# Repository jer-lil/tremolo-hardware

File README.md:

This is the hardware (PCB, MCAD) design for a tremolo pedal for guitar (or bass, synth, tonewheel organ, whatever you like). 
The firmware is here: https://github.com/jer-lil/tremolo-firmware/tree/main

This tremolo packs a lot of features into a very small (Hammond 125B, 65x120mm) enclosure.
Features include:

- All analog signal path
- Full stereo, with dedicated 1/4" jacks
- Harmonic tremolo
  - Continually adjustable LFO phase, allowing for sounds between mono/stereo/harmonic not found in other tremolo pedals (that I've discovered, please let me know if you know of any)
- Envelope control
  - The louder you play, the faster the tremolo goes. Or slower. Or stronger. Or the triangle wave warps towards a sawtooth. You decide.
- Expression pedal control
- Tap Tempo
  - Optional external tap signal
- "Ramp" mode, allowing user to ramp the rate up or down using a footswitch
- MIDI control

Note that at the time of writing, this project is still in progress.
As such, I have not been focusing on public documentation. If you have questions, please reach out.

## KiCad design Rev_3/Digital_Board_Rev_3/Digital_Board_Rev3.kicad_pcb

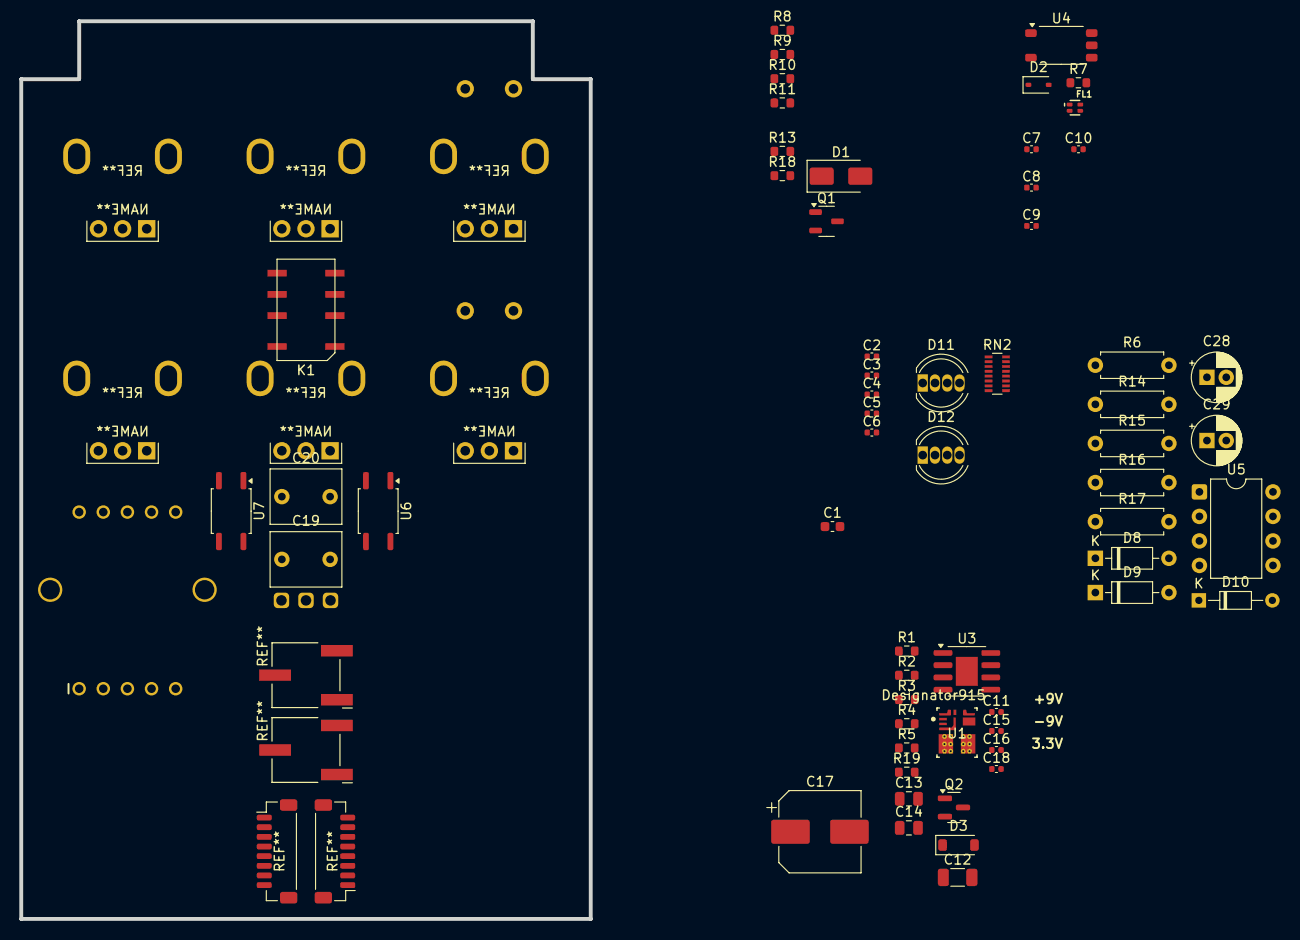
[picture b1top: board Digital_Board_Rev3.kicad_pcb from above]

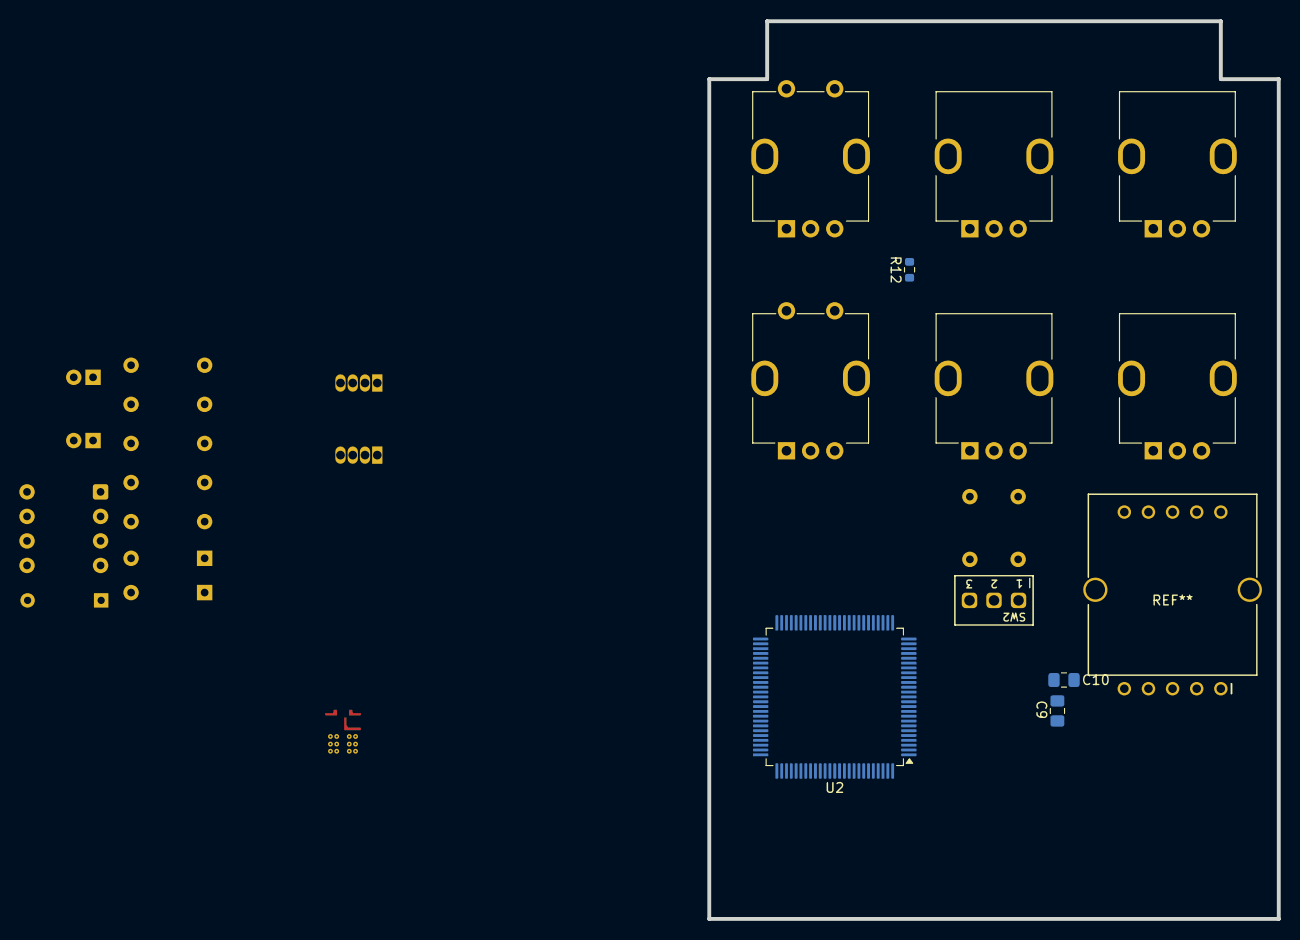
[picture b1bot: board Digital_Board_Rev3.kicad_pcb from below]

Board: 4 copper layers, 59.0 x 93.0 mm, 64 parts (5 on the bottom side), 41 nets, no tracks yet.

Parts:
C1: 2.2u; C_0603_1608Metric
C2, C3, C4, C5, C6, C7, C8, C9, C10, C16: 100n; C_0402_1005Metric
C9#2: 10n; C_0805_2012Metric_Pad1.18x1.45mm_HandSolder
C10#2: 1u; C_0805_2012Metric_Pad1.18x1.45mm_HandSolder
C11: 33n; C_0402_1005Metric
C12: 22u; C_1206_3216Metric
C13, C14: 10u; C_0805_2012Metric
C15: 1n; C_0402_1005Metric
C17: 100u; CP_Elec_8x6.2
C18: 22p; C_0402_1005Metric
C19, C20: 1u; C_Rect_L7.2mm_W5.5mm_P5.00mm_FKS2_FKP2_MKS2_MKP2
C28: 4.7u; CP_Radial_D5.0mm_P2.00mm
C29: 47u; CP_Radial_D5.0mm_P2.00mm
D1: B120-E3; D_SMA
D2: BAT54WS; D_SOD-323
D3: MMSZ5236B-7-F; D_SOD-123
D8, D9: 1N914; D_DO-35_SOD27_P7.62mm_Horizontal
D10: D_Zener; D_DO-34_SOD68_P7.62mm_Horizontal
D11, D12: LED_RGBA; LED_D5.0mm-4_RGB
FL1: FIL_EXC-24CB102U
K1: IM05GR; Relay_DPDT_TE_IM05GR
Q1: MMBT3904; SOT-23-3
Q2: DMP3099L; SOT-23
R1: 1; R_0603_1608Metric
R2: 180k; R_0603_1608Metric
R3: 43k; R_0603_1608Metric
R4: 68k; R_0603_1608Metric
R5: 15k; R_0603_1608Metric
R6: 3.3k; R_Axial_DIN0207_L6.3mm_D2.5mm_P7.62mm_Horizontal
R7, R9, R10: 330; R_0603_1608Metric
R8: 4.7k; R_0603_1608Metric
R11, R12: 1k; R_0603_1608Metric
R13, R18: 1M; R_0603_1608Metric
R14: 100k; R_Axial_DIN0207_L6.3mm_D2.5mm_P7.62mm_Horizontal
R15: 10k; R_Axial_DIN0207_L6.3mm_D2.5mm_P7.62mm_Horizontal
R16: 47k; R_Axial_DIN0207_L6.3mm_D2.5mm_P7.62mm_Horizontal
R17: 1k; R_Axial_DIN0207_L6.3mm_D2.5mm_P7.62mm_Horizontal
R19: 10k; R_0603_1608Metric
RN2: R_Pack08; R_Array_Convex_8x0602
SW2: SW_SPDT_MSM; SW_TOGGLE_ALPHA-200_SUBMINI_SPDT_PC-PINS
U1: TPSM84338RCJR; TI-RCJ0009A-MFG
U2: STM32G474VBTx; LQFP-100_14x14mm_P0.5mm
U3: ADP7142ARDZ; SOIC-8-1EP_3.9x4.9mm_P1.27mm_EP2.29x3mm
U4: TLP2361; SO-5-6_4.55x3.7mm_P1.27mm
U5: OPA2134; DIP-8_W7.62mm
U6, U7: TLP170AM; SO-4_4.4x3.9mm_P2.54mm

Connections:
+3.3V: R1.2, U4.6 (VDD)
+3V3: C1.1, C2.1, C3.1, C4.1, C5.1, C6.1, C9#2.1, C10#2.1, D11.4 (A), D12.4 (A), U2.24 (VDD), U2.37 (VDDA), U2.49 (VDD), U2.64 (VDD), U2.75 (VDD), U2.100 (VDD)
+9V: D1.1 (K), K1.1
/ENVELOPE/ENV_OUT: C29.2, D10.1 (K), R17.2
/Optos and LEDs/B1_R: D12.3 (BK), RN2.11 (R6.2)
/Optos and LEDs/B2_R: D11.3 (BK), RN2.14 (R3.2)
/Optos and LEDs/G1_R: D12.2 (GK), RN2.12 (R5.2)
/Optos and LEDs/G2_R: D11.2 (GK), RN2.15 (R2.2)
/Optos and LEDs/R1_R: D12.1 (RK), RN2.13 (R4.2)
/Optos and LEDs/R2_R: D11.1 (RK), RN2.16 (R1.2)
/Relay & Mute/MUTE: R9.1, R10.1
/Relay & Mute/OUT_L(dc): C19.1, K1.3
/Relay & Mute/OUT_L(r): C19.2, R12.1
/Relay & Mute/OUT_R: R11.2, R18.1
/Relay & Mute/OUT_R(dc): C20.1, K1.6
/Relay & Mute/OUT_R(r): C20.2, R11.1
/TAP & MIDI/MIDI_SINK(filt): D2.2 (A), FL1.3, U4.3 (K)
/TAP & MIDI/MIDI_SRC(filt): FL1.4, R7.1
/TAP & MIDI/MIDI_SRC(r)(filt): D2.1 (K), R7.2, U4.1 (A)
GND: C28.1, C29.1, D10.2 (A), R6.2, R16.2
GNDA: R13.2, R18.2, U2.35 (VSSA), U6.4, U7.4
GNDD: C1.2, C2.2, C3.2, C4.2, C5.2, C6.2, C7.2, C8.2, C9.2, C9#2.2, C10.2, C10#2.2, C11.2, C12.2, C13.2, C14.2, C15.2, C16.2, C17.2, Q1.2 (E), R2.2, R3.2, R5.2, R19.2, SW2.2, U1.3 (GND), U2.23 (VSS), U2.48 (VSS), U2.63 (VSS), U2.74 (VSS), U2.99 (VSS), U4.4 (GND), U6.3, U7.3
unnamed: D1.2 (A), K1.8, Q1.3 (C)
unnamed: D3.2 (A), Q2.1 (G), R19.1
unnamed: D8.2 (A), R6.1, R14.1, U5.2 (-)
unnamed: D8.1 (K), D9.2 (A), U5.1
unnamed: D9.1 (K), R14.2, R15.1
unnamed: Q1.1 (B), R8.2
unnamed: R10.2, U6.1
unnamed: R12.2, R13.1
unnamed: C18.2, R4.2, R5.1, U1.2 (FB)
unnamed: R2.1, U1.7 (MODE)
unnamed: R3.1, U1.9 (RT_SYNC)
unnamed: C11.1, U1.8 (SS_PG)
unnamed: C12.1, C13.1, C14.1, C15.1, C16.1, C17.1, C18.1, R1.1, R4.1, U1.4 (VOUT)
unnamed: U3.4 (GND), U3.9 (GND)
unnamed: U3.7 (VIN), U3.8 (VIN)
unnamed: U3.1 (VOUT), U3.2 (VOUT)
unnamed: C28.2, R15.2, R16.1, U5.5 (+)
unnamed: R17.1, U5.6 (-), U5.7
VIN_PROT: D3.1 (K), Q2.2 (S), U1.6 (VIN)

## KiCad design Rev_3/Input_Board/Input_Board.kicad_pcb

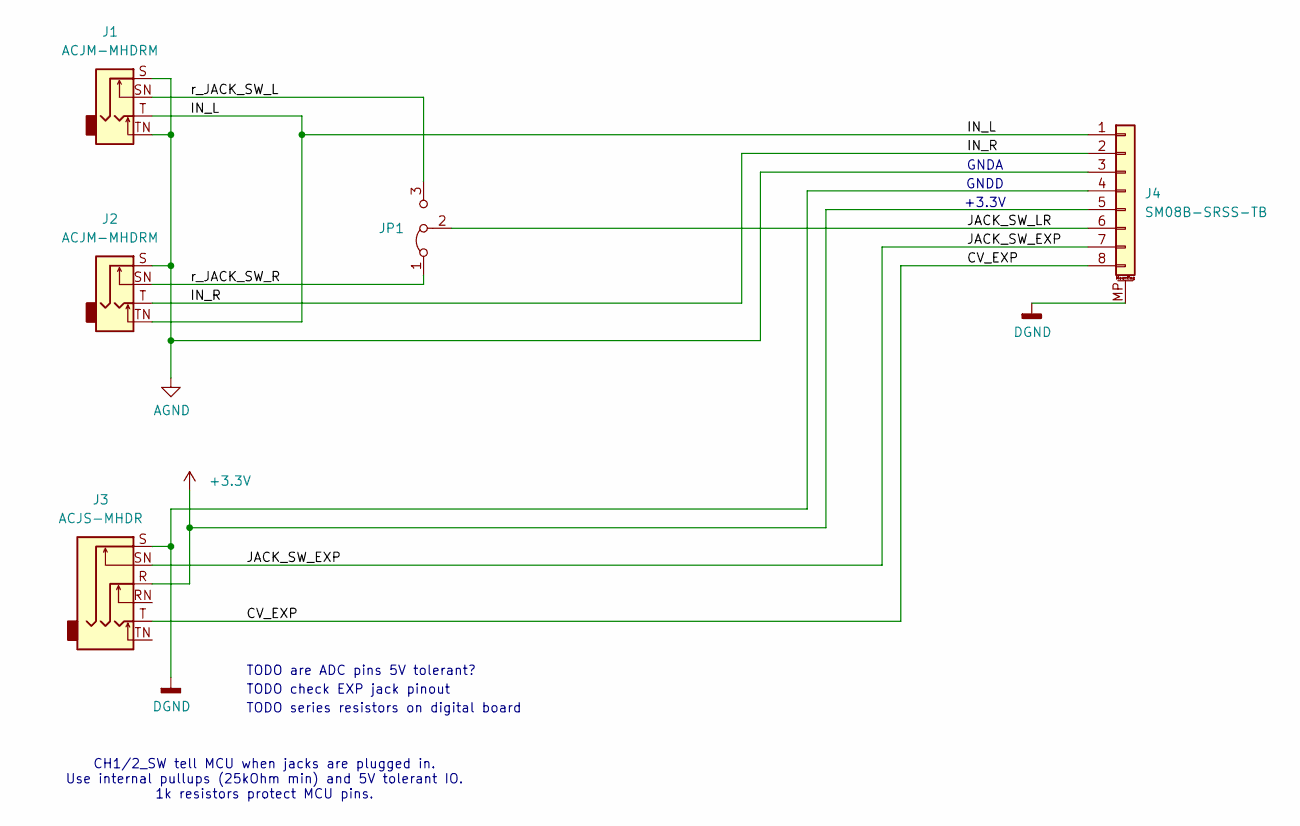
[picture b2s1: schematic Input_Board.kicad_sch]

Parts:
J1, J2: 6; Amphenol_ACJM-MHDR(M); MPN ACJM-MHDRM
J3: 6; Amphenol_ACJS-MHDR(M); MPN ACJS-MHDR
J4: 8; JST_SH_BM08B-SRSS-TB_1x08-1MP_P1.00mm_Vertical; MPN SM08B-SRSS-TB
JP1: Jumper_3_Bridged12; SolderJumper-3_P1.3mm_Bridged12_Pad1.0x1.5mm

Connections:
+3.3V: J3.R, J4.5
/CV_EXP: J3.T, J4.8
/IN_L: J1.T, J2.TN, J4.1
/IN_R: J2.T, J4.2
/JACK_SW_EXP: J3.SN, J4.7
/JACK_SW_LR: J4.6, JP1.2 (C)
/r_JACK_SW_L: J1.SN, JP1.3 (B)
/r_JACK_SW_R: J2.SN, JP1.1 (A)
AGND: J1.S, J1.TN, J2.S, J4.3
DGND: J3.S, J4.4, J4.MP (MountPin)

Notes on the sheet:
TODO series resistors on digital board
TODO check EXP jack pinout
GNDA
GNDD
TODO are ADC pins 5V tolerant?
+3.3V
CH1/2_SW tell MCU when jacks are plugged in. Use internal pullups (25kOhm min) and 5V tolerant IO. 1k resistors protect MCU pins.

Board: 2 copper layers, 5 parts (3 on the bottom side), 10 nets, no tracks yet.

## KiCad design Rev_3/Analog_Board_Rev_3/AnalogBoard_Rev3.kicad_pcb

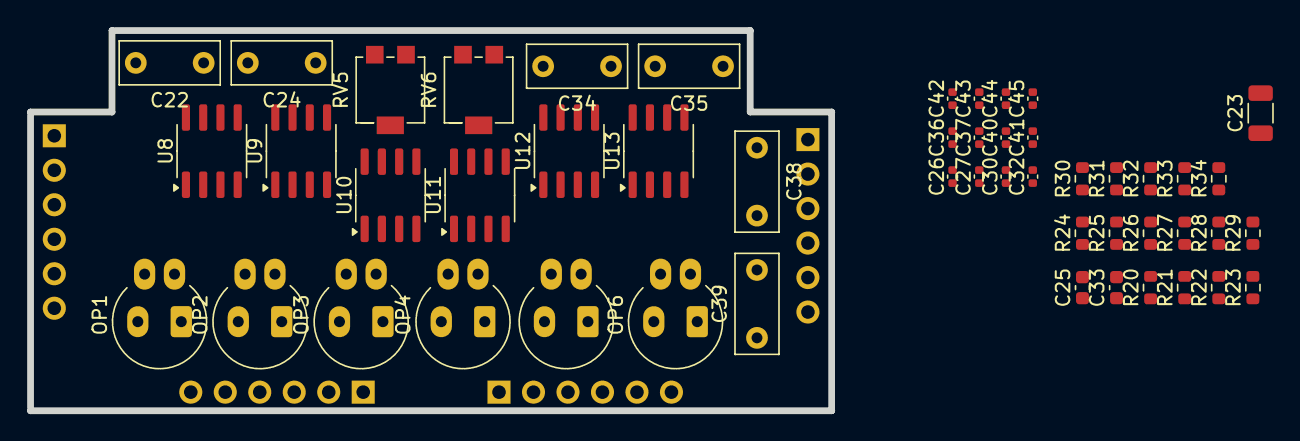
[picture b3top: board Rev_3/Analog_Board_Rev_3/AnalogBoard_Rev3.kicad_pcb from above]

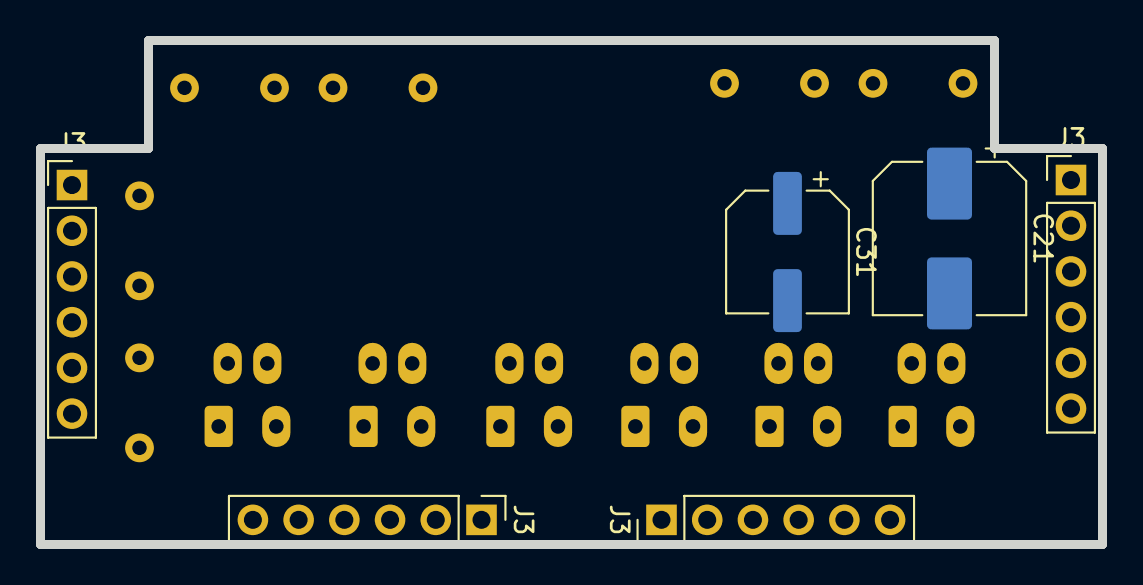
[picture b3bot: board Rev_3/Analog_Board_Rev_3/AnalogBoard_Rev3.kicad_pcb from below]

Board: 4 copper layers, 59.0 x 28.0 mm, 56 parts (6 on the bottom side), 29 nets, no tracks yet.

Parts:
C21: 100u; CP_Elec_8x6.2
C22, C24: 22n; C_Rect_L7.2mm_W3.0mm_P5.00mm_FKS2_FKP2_MKS2_MKP2
C23: 10u; C_1206_3216Metric
C25, C33: 1u; C_0603_1608Metric
C26, C27: 22p; C_0402_1005Metric
C30, C32, C36, C37, C40, C41, C42, C43, C44, C45: 100n; C_0402_1005Metric
C31: 10u; CP_Elec_6.3x5.8
C34, C35, C38, C39: 10n; C_Rect_L7.2mm_W3.0mm_P5.00mm_FKS2_FKP2_MKS2_MKP2
J3, J3#2, J3#3, J3#4: Conn_01x06_Male; PinHeader_1x06_P2.54mm_Vertical
OP1, OP2, OP3, OP4, OP5, OP6: NSL-32; Luna_NSL-32_Vertical
R20: 1; R_0603_1608Metric
R21, R22, R23, R24: 1M; R_0603_1608Metric
R25, R26: 100k; R_0603_1608Metric
R27, R28, R29, R30: 39k; R_0603_1608Metric
R31, R32: 100; R_0603_1608Metric
R33, R34: 330; R_0603_1608Metric
RV5, RV6: B1k; Potentiometer_Bourns_3214G_Horizontal
U8: TLE2426xD; SOIC-8_3.9x4.9mm_P1.27mm
U9, U10, U11, U12, U13: OPA1688IDR; SOIC-8_3.9x4.9mm_P1.27mm

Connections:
/Analog/BYP_L: C34.1, R27.1, U9.1, U9.2 (-)
/Analog/BYP_R: C35.1, R28.1, U10.1, U10.2 (-)
/Analog/EFF_L: R33.2, RV5.2, U13.7
/Analog/EFF_R: R34.2, RV6.2, U13.1
/Analog/HP_L: C34.2, R30.1, U12.5 (+)
/Analog/HP_OUT_L: OP2.4 (R), U12.6 (-), U12.7
/Analog/HP_OUT_R: OP4.4 (R), U11.6 (-), U11.7
/Analog/HP_R: C35.2, R29.1, U11.5 (+)
/Analog/IN_L: C24.1, R22.1
/Analog/IN_R: C22.1, R21.1
/Analog/LP_L: C39.2, R27.2, U12.3 (+)
/Analog/LP_OUT_L: OP1.4 (R), U12.1, U12.2 (-)
/Analog/LP_OUT_R: OP3.4 (R), U11.1, U11.2 (-)
/Analog/LP_R: C38.2, R28.2, U11.3 (+)
/Analog/SUM_L: OP1.3 (R), OP2.3 (R), R31.1, U9.6 (-)
/Analog/SUM_OUT_L: OP5.4 (R), R31.2, U9.7
/Analog/SUM_OUT_R: OP6.4 (R), R32.2, U10.7
/Analog/SUM_R: OP3.3 (R), OP4.3 (R), R32.1, U10.6 (-)
AGND: C21.2, C23.2, C25.2, C30.2, C31.2, C32.2, C33.2, C36.2, C37.2, C40.2, C41.2, C42.2, C43.2, C44.2, C45.2, R21.2, R22.2, U8.2 (COMMON), U9.4 (V-), U10.4 (V-), U11.4 (V-), U12.4 (V-), U13.4 (V-)
DGND: OP1.2 (K), OP2.2 (K), OP3.2 (K), OP4.2 (K), OP5.2 (K), OP6.2 (K)
unnamed: C22.2, R23.1, R25.1
unnamed: C24.2, R24.1, R26.1
unnamed: C25.1, U8.8 (NOISE_REDUCTION)
unnamed: C27.1, R26.2, U9.3 (+)
unnamed: C26.1, R25.2, U10.3 (+)
unnamed: OP6.3 (R), R34.1, RV6.1, U13.2 (-)
unnamed: OP5.3 (R), R33.1, RV5.1, U13.6 (-)
VCC: C21.1, C23.1, C30.1, C36.1, C40.1, C42.1, C44.1, R20.2, U8.3 (IN), U9.8 (V+), U10.8 (V+), U11.8 (V+), U12.8 (V+), U13.8 (V+)
VREF: C26.2, C27.2, C31.1, C32.1, C33.1, C37.1, C38.1, C39.1, C41.1, C43.1, C45.1, R23.2, R24.2, R29.2, R30.2, U8.1 (OUT), U9.5 (+), U10.5 (+), U13.3 (+), U13.5 (+)

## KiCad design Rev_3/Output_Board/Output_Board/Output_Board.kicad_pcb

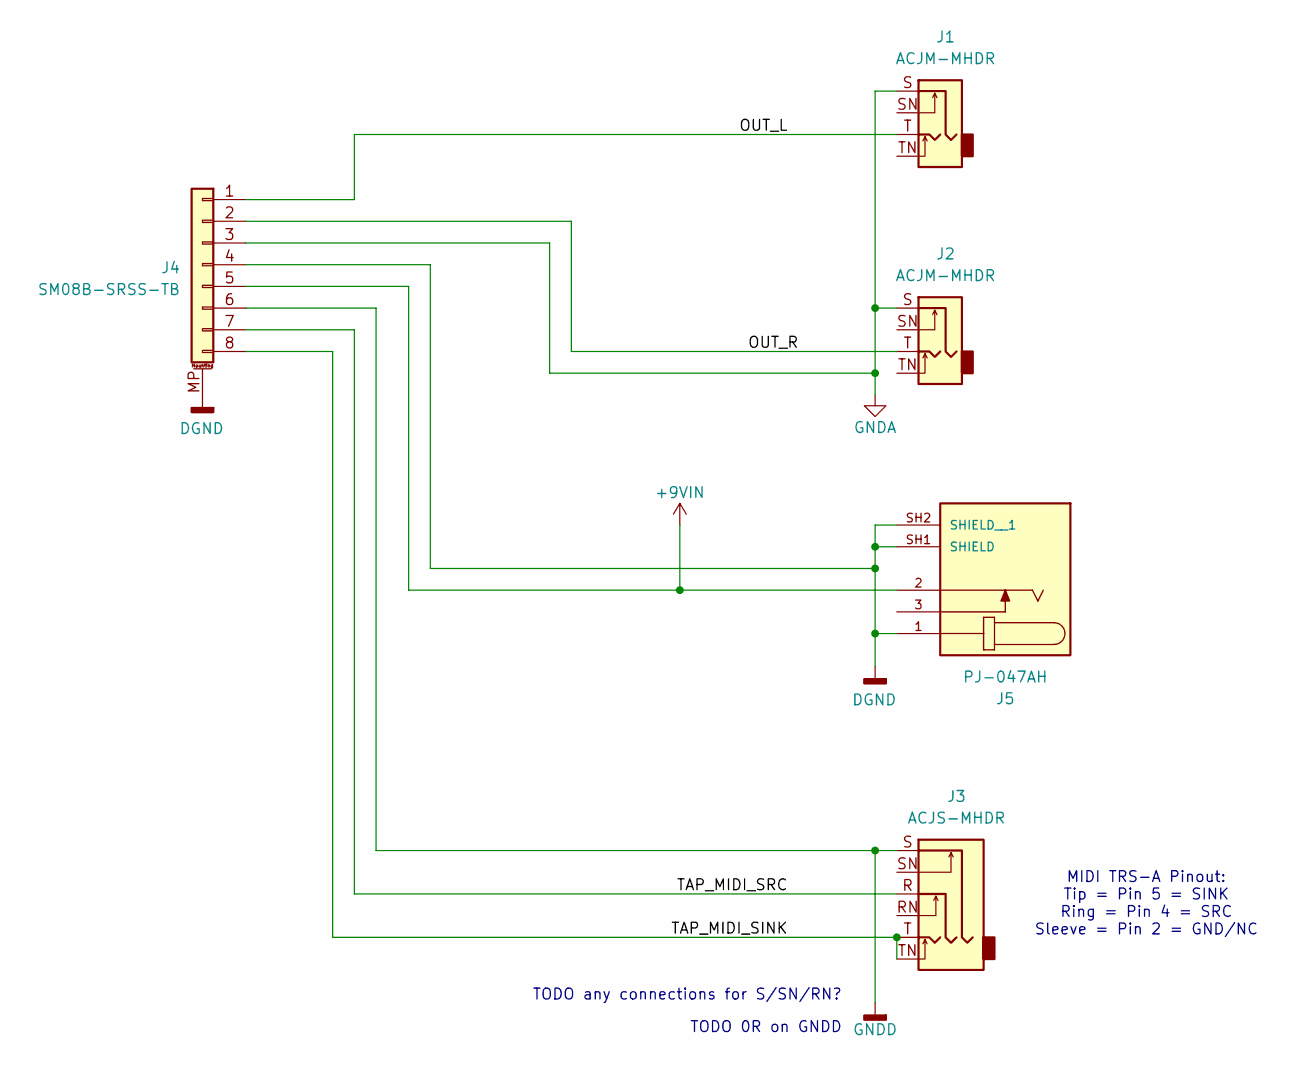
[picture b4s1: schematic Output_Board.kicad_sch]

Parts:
J1, J2: 6; Amphenol_ACJM-MHDR(M); MPN ACJM-MHDR
J3: 6; Amphenol_ACJS-MHDR(M); MPN ACJS-MHDR
J4: 8; JST_SH_BM08B-SRSS-TB_1x08-1MP_P1.00mm_Vertical; MPN SM08B-SRSS-TB
J5: 1; BarrelJack_CUI_PJ-047AH; PARTREV 1.06

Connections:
+9VIN: J4.5, J5.2
/OUT_L: J1.T, J4.1
/OUT_R: J2.T, J4.2
/TAP_MIDI_SINK: J3.T, J3.TN, J4.8
/TAP_MIDI_SRC: J3.R, J4.7
DGND: J4.4, J4.MP (MountPin), J5.1, J5.SH1 (SHIELD), J5.SH2 (SHIELD__1)
GNDA: J1.S, J2.S, J4.3
GNDD: J3.S, J4.6

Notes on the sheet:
TODO 0R on GNDD
TODO any connections for S/SN/RN?
MIDI TRS-A Pinout: Tip = Pin 5 = SINK Ring = Pin 4 = SRC Sleeve = Pin 2 = GND/NC

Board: 2 copper layers, 5 parts (4 on the bottom side), 8 nets, no tracks yet.

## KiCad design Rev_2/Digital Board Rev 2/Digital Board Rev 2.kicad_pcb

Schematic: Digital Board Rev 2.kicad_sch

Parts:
C1: 4.7u; C_0805_2012Metric_Pad1.18x1.45mm_HandSolder
C2, C3: 18p; C_0805_2012Metric_Pad1.18x1.45mm_HandSolder
C4, C5, C6, C7, C8, C17, C20: 100n; C_0805_2012Metric_Pad1.18x1.45mm_HandSolder
C9: 10n; C_0805_2012Metric_Pad1.18x1.45mm_HandSolder
C10: 1u; C_0805_2012Metric_Pad1.18x1.45mm_HandSolder
J1, J2: Conn_01x02_Male; PinHeader_1x02_P2.54mm_Vertical
J3: Conn_01x06_Male; PinHeader_1x06_P2.54mm_Vertical
J4: Conn_01x08_Female; PinSocket_1x08_P2.54mm_Vertical
J11: Conn_01x10_Female; PinSocket_1x10_P2.54mm_Vertical
J13, J14: Conn_01x06_Female; PinSocket_1x06_P2.54mm_Vertical
J15: Conn_01x03_Male; PinHeader_1x03_P2.54mm_Vertical
JP1: Jumper; SolderJumper-2_P1.3mm_Bridged2Bar_Pad1.0x1.5mm
NT1, NT2, NT3, NT4: Net-Tie_2; NetTie-2_SMD_Pad0.5mm
R1: 10k; R_0805_2012Metric_Pad1.20x1.40mm_HandSolder
R2, R3, R4, R5, R10, R11: 330; R_0805_2012Metric_Pad1.20x1.40mm_HandSolder
U1: STM32F303R6Tx; LQFP-64_10x10mm_P0.5mm
Y1: 8MHz; Crystal_HC49-U_Vertical

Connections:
+3V3: C1.1, C4.1, C6.1, C7.1, C8.1, C9.1, C10.1, J3.1, J11.9, U1.13 (VDDA), U1.19 (VDD), U1.32 (VDD), U1.48 (VDD), U1.64 (VDD); also elsewhere on the board
+9V: J4.7; also elsewhere on the board
-9V: J4.4; also elsewhere on the board
/BYP: J1.2, U1.44 (PA11)
/CH1_BYP: J11.2; also elsewhere on the board
/CH1_EFF: J11.3; also elsewhere on the board
/CH1_IN: J11.1; also elsewhere on the board
/CH1_SW: U1.51 (PC10); also elsewhere on the board
/CH2_BYP: J4.2; also elsewhere on the board
/CH2_EFF: J4.3; also elsewhere on the board
/CH2_IN: J4.1; also elsewhere on the board
/CH2_SW: U1.52 (PC11); also elsewhere on the board
/DEPTH: U1.15 (PA1); also elsewhere on the board
/DIP1: J11.8, U1.26 (PB0)
/DIP2: J11.7, U1.27 (PB1)
/DIP3: J11.6, U1.28 (PB2)
/DIP4: J11.5, U1.43 (PA10)
/ENV_MODE_1: U1.34 (PB13); also elsewhere on the board
/ENV_MODE_2: U1.35 (PB14); also elsewhere on the board
/EXP: U1.9 (PC1); also elsewhere on the board
/EXP_SW: U1.42 (PA9); also elsewhere on the board
/HARM_MODE_1: U1.62 (PB9); also elsewhere on the board
/HARM_MODE_2: U1.29 (PB10); also elsewhere on the board
/LED1_B: U1.53 (PC12); also elsewhere on the board
/LED1_G: U1.54 (PD2); also elsewhere on the board
/LED1_R: U1.56 (PB4); also elsewhere on the board
/LED2_B: U1.57 (PB5); also elsewhere on the board
/LED2_G: U1.58 (PB6); also elsewhere on the board
/LED2_R: U1.59 (PB7); also elsewhere on the board
/MUTE1: U1.2 (PC13); also elsewhere on the board
/MUTE2: U1.3 (PC14); also elsewhere on the board
/NRST: C5.1, J3.5, U1.7 (NRST)
/OFFSET: U1.17 (PA3); also elsewhere on the board
/OSC1: C2.2, U1.5 (PF0), Y1.2
/OSC2: C3.2, U1.6 (PF1), Y1.1
/PAN_MODE_1: U1.30 (PB11); also elsewhere on the board
/PAN_MODE_2: U1.33 (PB12); also elsewhere on the board
/PWM1: R2.1, U1.22 (PA6)
/PWM2: R3.1, U1.20 (PA4)
/PWM3: R4.1, U1.39 (PC8)
/PWM4: R5.1, U1.40 (PC9)
/PWM_OUT_1: J13.1, R2.2
/PWM_OUT_2: J13.3, R3.2
/PWM_OUT_3: J14.2, R4.2
/PWM_OUT_4: J14.4, R5.2
/PWM_OUT_VOL_1: J13.5, R10.2
/PWM_OUT_VOL_2: J14.6, R11.2
/PWM_RTN_1: J13.2, NT1.1
/PWM_RTN_2: J13.4, NT2.1
/PWM_RTN_3: J14.1, NT3.1
/PWM_RTN_4: J14.3, NT4.1
/PWM_RTN_VOL_1: J13.6
/PWM_RTN_VOL_2: J14.5
/PWM_VOL_1: R10.1, U1.21 (PA5)
/PWM_VOL_2: R11.1, U1.55 (PB3)
/RATE: U1.14 (PA0); also elsewhere on the board
/RLY_SET: U1.50 (PA15); also elsewhere on the board
/SHAPE: U1.16 (PA2); also elsewhere on the board
/SUBDIV: U1.8 (PC0); also elsewhere on the board
/SWCLK: J3.2, U1.49 (PA14)
/SWDIO: J3.4, U1.46 (PA13)
/TAP: J2.2, U1.45 (PA12)
/TAP_EXT: U1.37 (PC6); also elsewhere on the board
/TRIM1: C17.1, J4.6, U1.10 (PC2)
/TRIM2: C20.1, J4.5, U1.11 (PC3)
/UART_RX: J15.2, U1.25 (PC5)
/UART_TX: J15.3, U1.24 (PC4)
/VOL: U1.23 (PA7); also elsewhere on the board
GNDA: J4.8, J11.10, JP1.2; also elsewhere on the board
GNDD: C1.2, C2.1, C3.1, C4.2, C5.2, C6.2, C7.2, C8.2, C9.2, C10.2, C17.2, C20.2, J1.1, J2.1, J3.3, J11.4, J15.1, JP1.1, NT1.2, NT2.2, NT3.2, NT4.2, R1.1, U1.12 (VSSA), U1.18 (VSS), U1.31 (VSS), U1.47 (VSS), U1.63 (VSS); also elsewhere on the board
unnamed: R1.2, U1.60 (BOOT0)

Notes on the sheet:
TAP_EXT on 5V tolerant pin

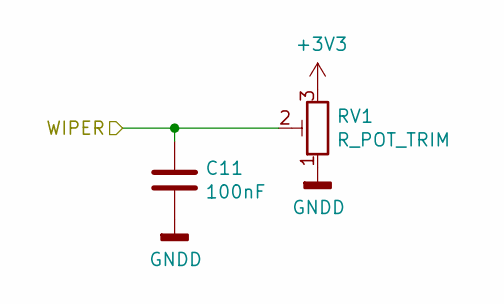
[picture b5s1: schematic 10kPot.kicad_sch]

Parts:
C11: 100nF; C_0805_2012Metric_Pad1.18x1.45mm_HandSolder
RV1: R_POT_TRIM; Potentiometer_9MM

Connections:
+3V3: RV1.3; also elsewhere on the board
/RATE: C11.1, RV1.2; also elsewhere on the board
GNDD: C11.2, RV1.1; also elsewhere on the board

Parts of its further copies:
C12, C13, C14, C15, C26: 100nF; C_0805_2012Metric_Pad1.18x1.45mm_HandSolder
RV2, RV3, RV4, RV5, RV10: R_POT_TRIM; Potentiometer_9MM

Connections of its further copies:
+3V3: RV2.3, RV3.3, RV4.3, RV5.3, RV10.3; also elsewhere on the board
/DEPTH: C12.1, RV2.2; also elsewhere on the board
/OFFSET: C14.1, RV4.2; also elsewhere on the board
/SHAPE: C13.1, RV3.2; also elsewhere on the board
/SUBDIV: C15.1, RV5.2; also elsewhere on the board
/VOL: C26.1, RV10.2; also elsewhere on the board
GNDD: C12.2, C13.2, C14.2, C15.2, C26.2, RV2.1, RV3.1, RV4.1, RV5.1, RV10.1; also elsewhere on the board

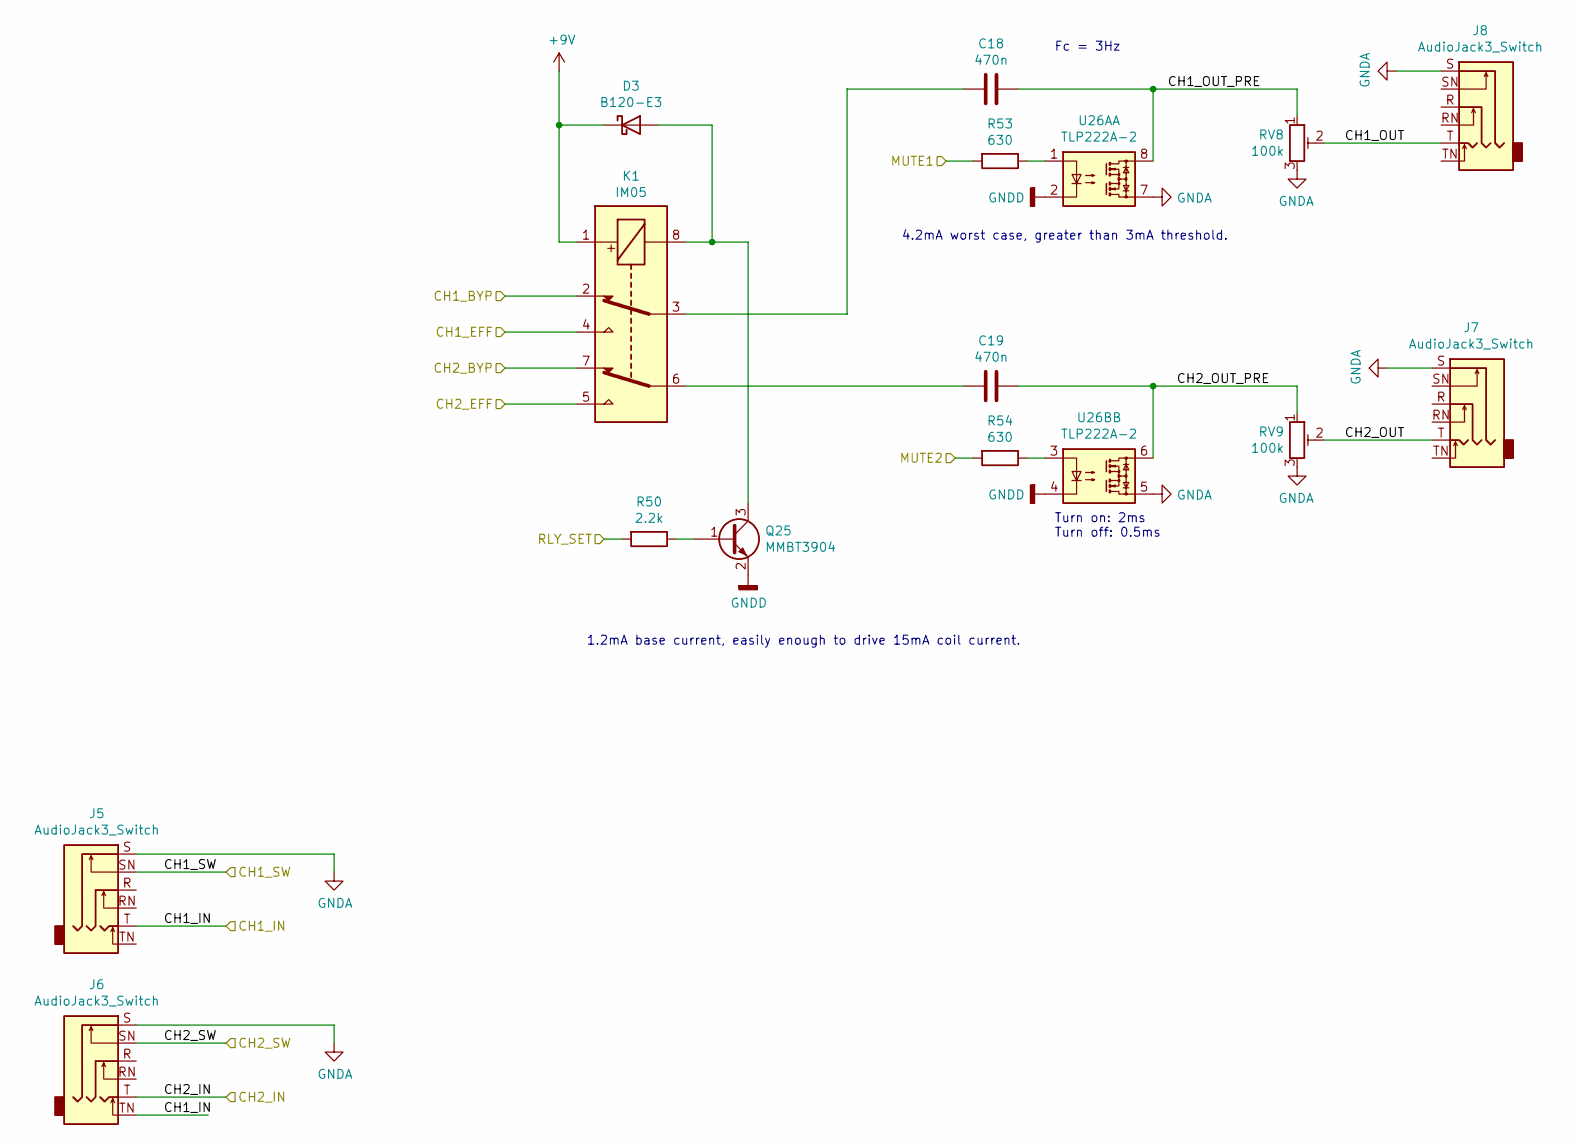
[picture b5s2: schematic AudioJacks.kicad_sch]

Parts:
C18, C19: 470n; C_0805_2012Metric_Pad1.18x1.45mm_HandSolder
D3: B120-E3; D_SMA
J5, J6, J7, J8: AudioJack3_Switch; Jack_0.25in_TRS_Switched
K1: IM05; Relay_DPDT_NL_TE_IM05GR
Q25: MMBT3904; SOT-23
R50: 2.2k; R_0805_2012Metric_Pad1.20x1.40mm_HandSolder
R53, R54: 630; R_0805_2012Metric_Pad1.20x1.40mm_HandSolder
RV8, RV9: 100k; Potentiometer_Bourns_3314G_Vertical
U26A, U26B: TLP222A-2; DIP-8_W7.62mm

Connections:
+9V: D3.1 (K), K1.1; also elsewhere on the board
/Audio Jacks/CH1_OUT: J8.T, RV8.2
/Audio Jacks/CH1_OUT_PRE: C18.1, RV8.1, U26A.8; also elsewhere on the board
/Audio Jacks/CH2_OUT: J7.T, RV9.2
/Audio Jacks/CH2_OUT_PRE: C19.1, RV9.1, U26B.6; also elsewhere on the board
/CH1_BYP: K1.2; also elsewhere on the board
/CH1_EFF: K1.4; also elsewhere on the board
/CH1_IN: J5.T, J6.TN; also elsewhere on the board
/CH1_SW: J5.SN; also elsewhere on the board
/CH2_BYP: K1.7; also elsewhere on the board
/CH2_EFF: K1.5; also elsewhere on the board
/CH2_IN: J6.T; also elsewhere on the board
/CH2_SW: J6.SN; also elsewhere on the board
/MUTE1: R53.2; also elsewhere on the board
/MUTE2: R54.2; also elsewhere on the board
/RLY_SET: R50.2; also elsewhere on the board
GNDA: J5.S, J6.S, J7.S, J8.S, RV8.3, RV9.3, U26A.7, U26B.5; also elsewhere on the board
GNDD: Q25.2 (E), U26A.2, U26B.4; also elsewhere on the board
unnamed: C18.2, K1.3
unnamed: C19.2, K1.6
unnamed: D3.2 (A), K1.8, Q25.3 (C)
unnamed: Q25.1 (B), R50.1
unnamed 115: R53.1, U26A.1; also elsewhere on the board
unnamed 116: R54.1, U26B.3; also elsewhere on the board

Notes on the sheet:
1.2mA base current, easily enough to drive 15mA coil current.
Turn on: 2ms Turn off: 0.5ms
4.2mA worst case, greater than 3mA threshold.
Fc = 3Hz

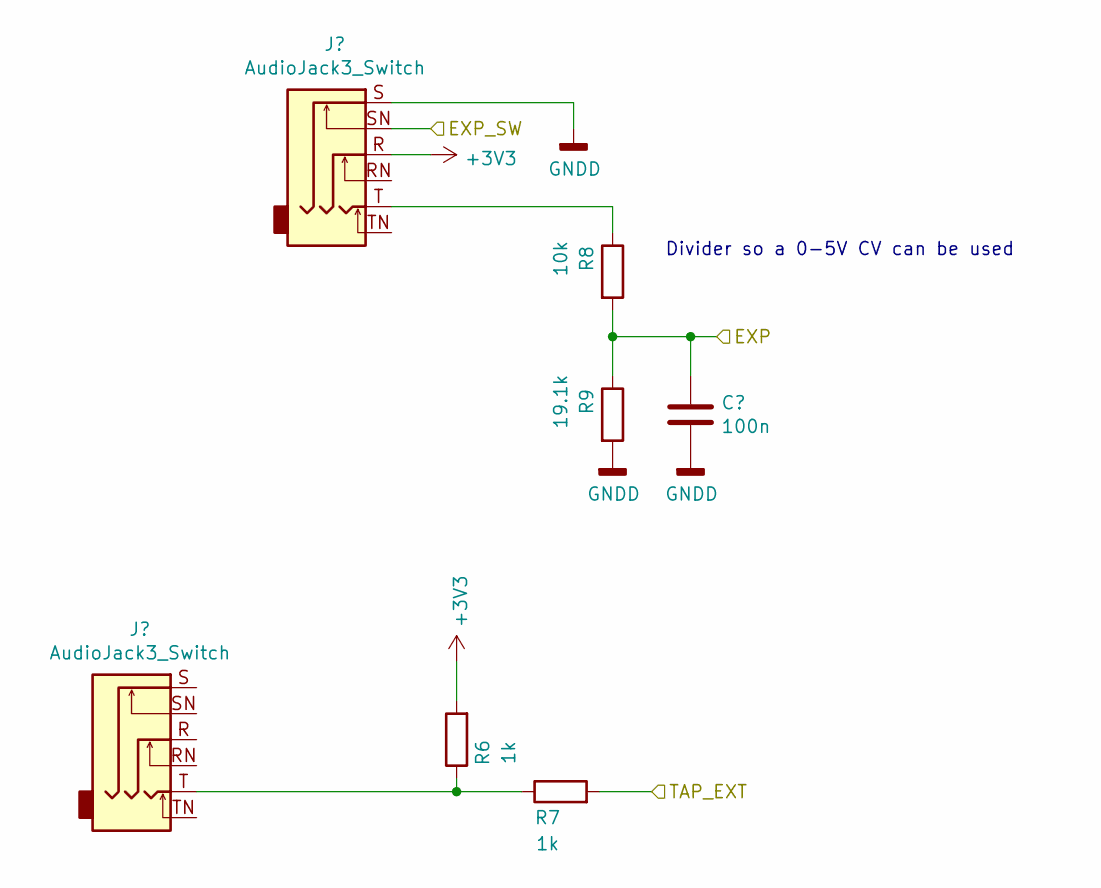
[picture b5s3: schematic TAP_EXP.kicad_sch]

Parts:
C16: 100n; C_0805_2012Metric_Pad1.18x1.45mm_HandSolder
J9, J10: AudioJack3_Switch; Jack_0.25in_TRS_Switched
R6, R7: 1k; R_0805_2012Metric_Pad1.20x1.40mm_HandSolder
R8: 10k; R_0805_2012Metric_Pad1.20x1.40mm_HandSolder
R9: 19.1k; R_0805_2012Metric_Pad1.20x1.40mm_HandSolder

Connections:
+3V3: J9.R, R6.2; also elsewhere on the board
/EXP: C16.1, R8.2, R9.1; also elsewhere on the board
/EXP_SW: J9.SN; also elsewhere on the board
/TAP_EXT: R7.2; also elsewhere on the board
GNDD: C16.2, J9.S, R9.2; also elsewhere on the board
unnamed: J9.T, R8.1
unnamed: J10.T, R6.1, R7.1

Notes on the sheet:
Divider so a 0-5V CV can be used

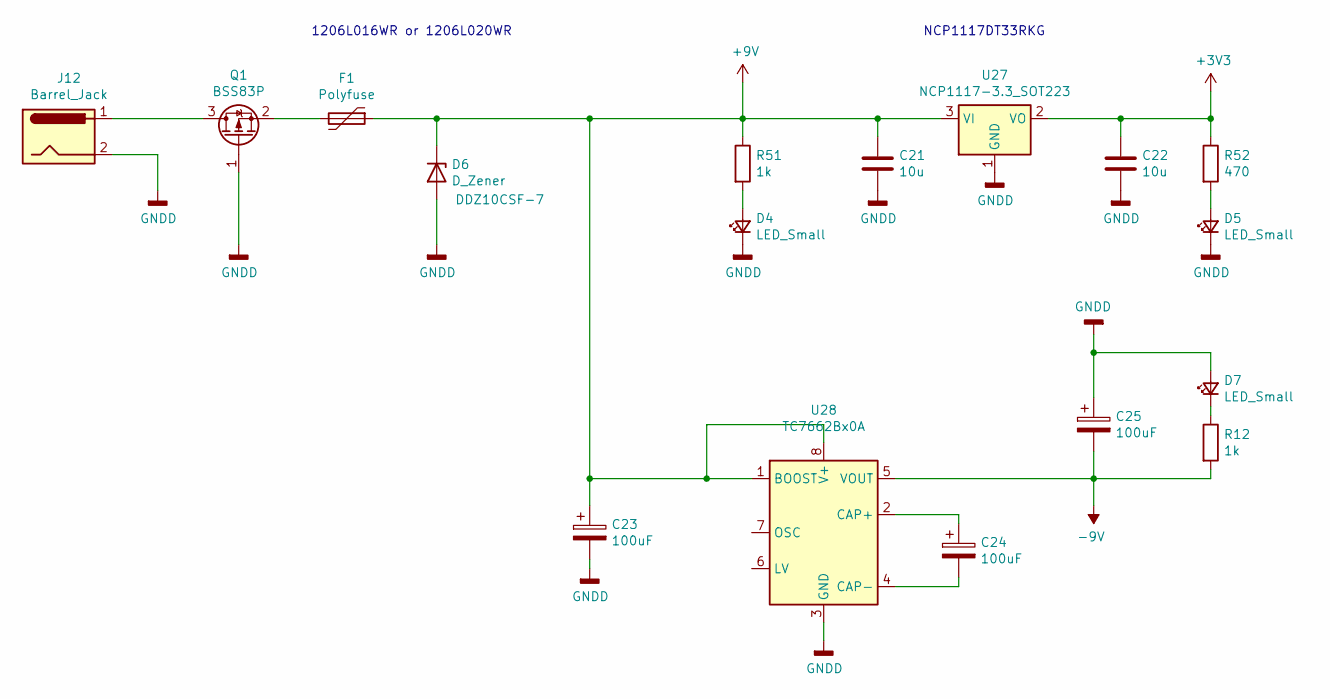
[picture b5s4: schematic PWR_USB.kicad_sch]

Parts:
C21, C22: 10u; C_1206_3216Metric_Pad1.33x1.80mm_HandSolder
C23, C24, C25: 100uF; CP_Radial_D5.0mm_P2.00mm
D4, D5, D7: LED_Small; LED_0805_2012Metric_Castellated
D6: D_Zener; D_SMA_Handsoldering; MPN DDZ10CSF-7
F1: Polyfuse; Fuse_1206_3216Metric_Pad1.42x1.75mm_HandSolder
J12: Barrel_Jack; BarrelJack_CUI_PJ-063AH_Horizontal_CircularHoles
Q1: BSS83P; SOT-23
R12, R51: 1k; R_0805_2012Metric_Pad1.20x1.40mm_HandSolder
R52: 470; R_0805_2012Metric_Pad1.20x1.40mm_HandSolder
U27: NCP1117-3.3_SOT223; SOT-223-3_TabPin2; MPN NCP1117DT33RKG
U28: TC7662Bx0A; SOIC-8_3.9x4.9mm_P1.27mm

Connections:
+3V3: C22.1, R52.1, U27.2 (VO); also elsewhere on the board
+9V: C21.1, C23.1, D6.1 (K), F1.1, R51.1, U27.3 (VI), U28.1 (BOOST), U28.8 (V+); also elsewhere on the board
-9V: C25.2, R12.2, U28.5 (VOUT); also elsewhere on the board
GNDD: C21.2, C22.2, C23.2, C25.1, D4.1 (K), D5.1 (K), D6.2 (A), D7.2 (A), J12.2, Q1.1 (G), U27.1 (GND), U28.3 (GND); also elsewhere on the board
unnamed: C24.1, U28.2 (CAP+)
unnamed: C24.2, U28.4 (CAP-)
unnamed: D4.2 (A), R51.2
unnamed: D5.2 (A), R52.2
unnamed: D7.1 (K), R12.1
unnamed: F1.2, Q1.2 (S)
unnamed: J12.1, Q1.3 (D)

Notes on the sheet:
1206L016WR or 1206L020WR
NCP1117DT33RKG

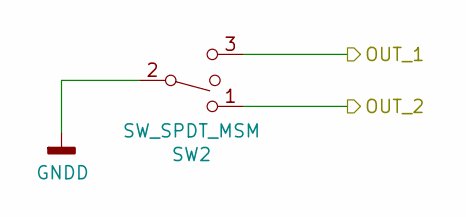
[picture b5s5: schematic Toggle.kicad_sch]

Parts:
SW2: SW_SPDT_MSM; SW_Toggle_SPDT

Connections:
/PAN_MODE_1: SW2.3; also elsewhere on the board
/PAN_MODE_2: SW2.1; also elsewhere on the board
GNDD: SW2.2; also elsewhere on the board

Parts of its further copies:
SW1, SW3: SW_SPDT_MSM; SW_Toggle_SPDT

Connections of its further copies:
/ENV_MODE_1: SW3.3; also elsewhere on the board
/ENV_MODE_2: SW3.1; also elsewhere on the board
/HARM_MODE_1: SW1.3; also elsewhere on the board
/HARM_MODE_2: SW1.1; also elsewhere on the board
GNDD: SW1.2, SW3.2; also elsewhere on the board
